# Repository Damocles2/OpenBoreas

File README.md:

# OpenBoreas
OpenBoreas is a smart solar/battery powered weather station control board desgined for everyone!
With wifi connectivity,40.4ma power consumption (that's a 100 hours of use from a a few hours of sunlight and a 4000mah battery!) and others impressive features,this little board is sure to fit your needs!

It's small size and open source nature makes sure that everyone can use it the way they please! Just connect it to a solar panel and battery and you're all set!

And when you complete that,it's easy to use android app will allow even the most inexperienced users to enjoy it!

Requires bluetoothserial, download it here: https://github.com/espressif/arduino-esp32/tree/master/libraries/BluetoothSerial

# Why did you name it that? 
Boreas is the roman god of the cool north wind. I believe that is related to this device.

# How much does it cost to produce?
Around 25$ depending on how cheap you can get the  esp32 and its surrounding chips

# I cant open those gerber files!
Those are gerber x2 files. Use an online converter or something. Also make sure to put them in a zip file before ordering.

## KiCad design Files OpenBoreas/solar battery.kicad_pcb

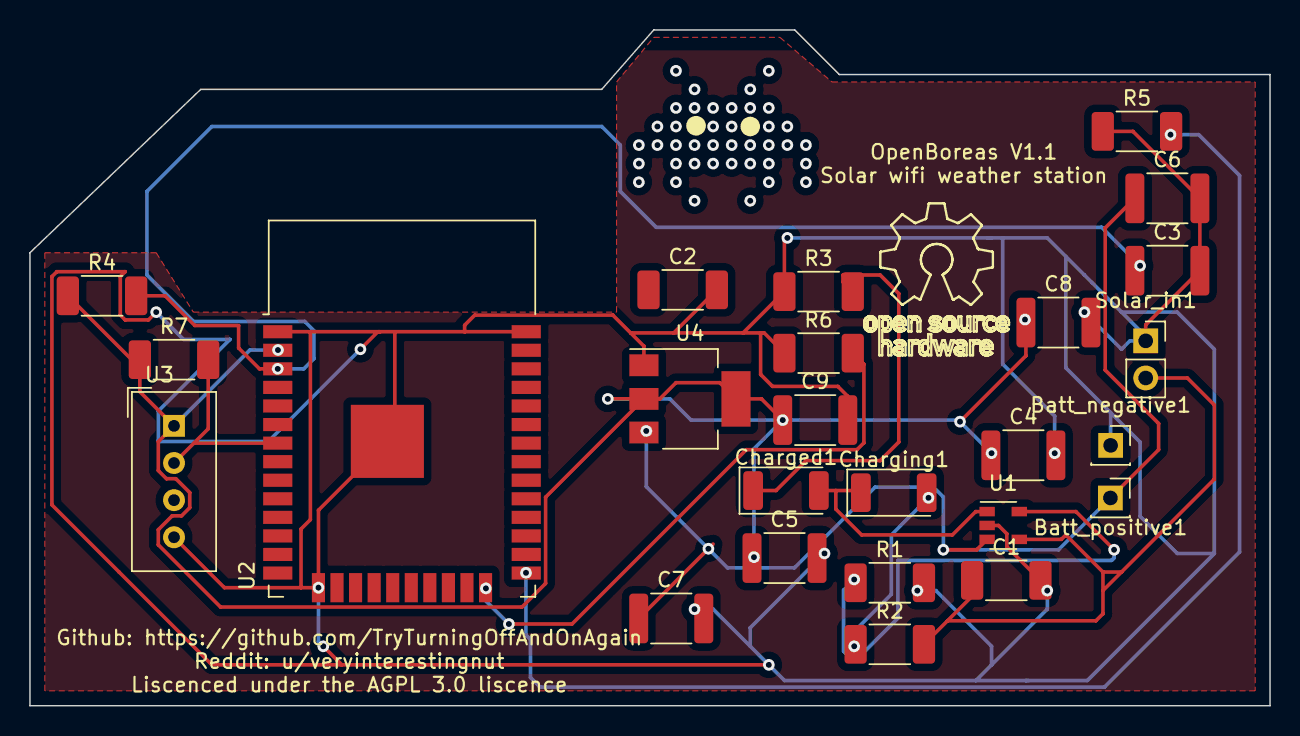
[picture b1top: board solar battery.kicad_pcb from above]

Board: 2 copper layers, 84.8 x 46.2 mm, 25 parts (0 on the bottom side), 12 nets.

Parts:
Batt_negative1: Conn_01x01_Female; PinSocket_1x01_P2.54mm_Vertical
Batt_positive1: Conn_01x01_Female; PinSocket_1x01_P2.54mm_Vertical
C1, C2: 10uF; C_2010_5025Metric_Pad1.52x2.65mm_HandSolder
C3: 1nF; C_1812_4532Metric_Pad1.30x3.40mm_HandSolder
C4: 0.1uF; C_1812_4532Metric_Pad1.30x3.40mm_HandSolder
C5: 10uF; C_1812_4532Metric_Pad1.30x3.40mm_HandSolder
C6, C8: 4.7uF; C_1812_4532Metric_Pad1.30x3.40mm_HandSolder
C7, C9: 1uF; C_1812_4532Metric_Pad1.30x3.40mm_HandSolder
Charged1: GREEN; LED_2010_5025Metric
Charging1: RED; LED_2010_5025Metric
R1: 2k; R_2010_5025Metric_Pad1.52x2.65mm_HandSolder
R2, R3: 470; R_2010_5025Metric_Pad1.52x2.65mm_HandSolder
R4: 12k; R_2010_5025Metric_Pad1.52x2.65mm_HandSolder
R5, R6: 5k; R_2010_5025Metric_Pad1.52x2.65mm_HandSolder
R7: 10k; R_2010_5025Metric_Pad1.52x2.65mm_HandSolder
Solar_in1: Conn_01x02_Female; PinSocket_1x02_P2.54mm_Vertical
U1: MCP73831-5-OT; SOT-23-5
U2: ESP32-WROOM-32
U3: DHT11; Aosong_DHT11_5.5x12.0_P2.54mm
U4: AMS1117-3.3; SOT-223-3_TabPin2

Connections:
+3V3: C4.1, C5.1, C8.1, C9.1, R4.1, R7.1, U2.2, U3.1, U4.2
Battery-out: Batt_positive1.1, C2.1, C6.1, C7.1, U1.3, U4.3
Data_temp: R7.2, U2.7, U3.2
GND: Batt_negative1.1, C1.2, C2.2, C3.2, C4.2, C5.2, C6.2, C7.2, C8.2, C9.2, R1.2, R3.1, R5.1, R6.1, Solar_in1.1, U1.2, U2.1, U2.15, U2.38, U2.39, U3.4, U4.1
unnamed: C1.1, R2.2, Solar_in1.2, U1.4
unnamed: C3.1, R4.2, U2.3
unnamed: Charged1.1, R3.2
unnamed: Charged1.2, Charging1.1, U1.1
unnamed: Charging1.2, R2.1
unnamed: R1.1, U1.5
unnamed: R5.2, U2.25
unnamed: R6.2, U2.24

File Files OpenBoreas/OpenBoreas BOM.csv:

"Id";"Designator";"Package";"Quantity";"Designation";"Supplier and ref";
1;"Batt_negative1,Batt_positive1";"PinSocket_1x01_P2.54mm_Vertical";2;"Conn_01x01_Female";;;
2;"C1,C2";"C_2010_5025Metric_Pad1.52x2.65mm_HandSolder";2;"10uF";;;
3;"C3";"C_1812_4532Metric_Pad1.30x3.40mm_HandSolder";1;"1nF";;;
4;"C4";"C_1812_4532Metric_Pad1.30x3.40mm_HandSolder";1;"0.1uF";;;
5;"C5";"C_1812_4532Metric_Pad1.30x3.40mm_HandSolder";1;"10uF";;;
6;"C6,C8";"C_1812_4532Metric_Pad1.30x3.40mm_HandSolder";2;"4.7uF";;;
7;"C7,C9";"C_1812_4532Metric_Pad1.30x3.40mm_HandSolder";2;"1uF";;;
8;"Charged1";"LED_2010_5025Metric";1;"GREEN";;;
9;"Charging1";"LED_2010_5025Metric";1;"RED";;;
10;"R1";"R_2010_5025Metric_Pad1.52x2.65mm_HandSolder";1;"2k";;;
11;"R2,R3";"R_2010_5025Metric_Pad1.52x2.65mm_HandSolder";2;"470";;;
12;"R4";"R_2010_5025Metric_Pad1.52x2.65mm_HandSolder";1;"12k";;;
13;"R5,R6";"R_2010_5025Metric_Pad1.52x2.65mm_HandSolder";2;"5k";;;
14;"R7";"R_2010_5025Metric_Pad1.52x2.65mm_HandSolder";1;"10k";;;
15;"Solar_in1";"PinSocket_1x02_P2.54mm_Vertical";1;"Conn_01x02_Female";;;
16;"U1";"SOT-23-5";1;"MCP73831-5-OT";;;
17;"U2";"ESP32-WROOM-32";1;"ESP32-WROOM-32";;;
18;"U3";"Aosong_DHT11_5.5x12.0_P2.54mm";1;"DHT11";;;
19;"U4";"SOT-223-3_TabPin2";1;"AMS1117-3.3";;;

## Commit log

2020-10-21 Relaxed with licence, affero was too damn strict for yall
2021-06-27 Create LICENSE

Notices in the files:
Files OpenBoreas/solar battery.kicad_pcb:
Liscenced under the AGPL 3.0 liscence
